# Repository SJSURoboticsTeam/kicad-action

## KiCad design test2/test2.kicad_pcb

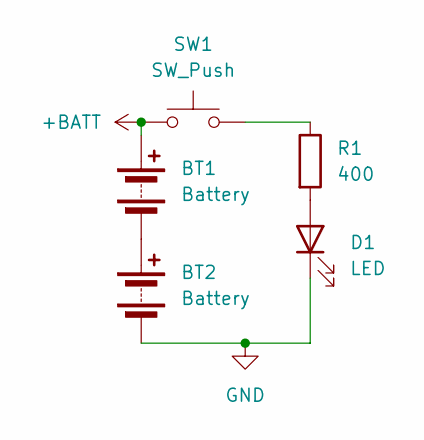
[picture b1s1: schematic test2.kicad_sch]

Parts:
BT1, BT2: Battery; BatteryHolder_Keystone_2466_1xAAA
D1: LED; LED_PLCC-2_3.4x3.0mm_KA
R1: 400; R_0603_1608Metric
SW1: SW_Push; SW_Push_1TS009xxxx-xxxx-xxxx_6x6x5mm

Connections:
+BATT: BT1.1 (+), SW1.1
GND: BT2.2 (-), D1.1 (K)
unnamed: BT1.2 (-), BT2.1 (+)
unnamed: D1.2 (A), R1.2
unnamed: R1.1, SW1.2

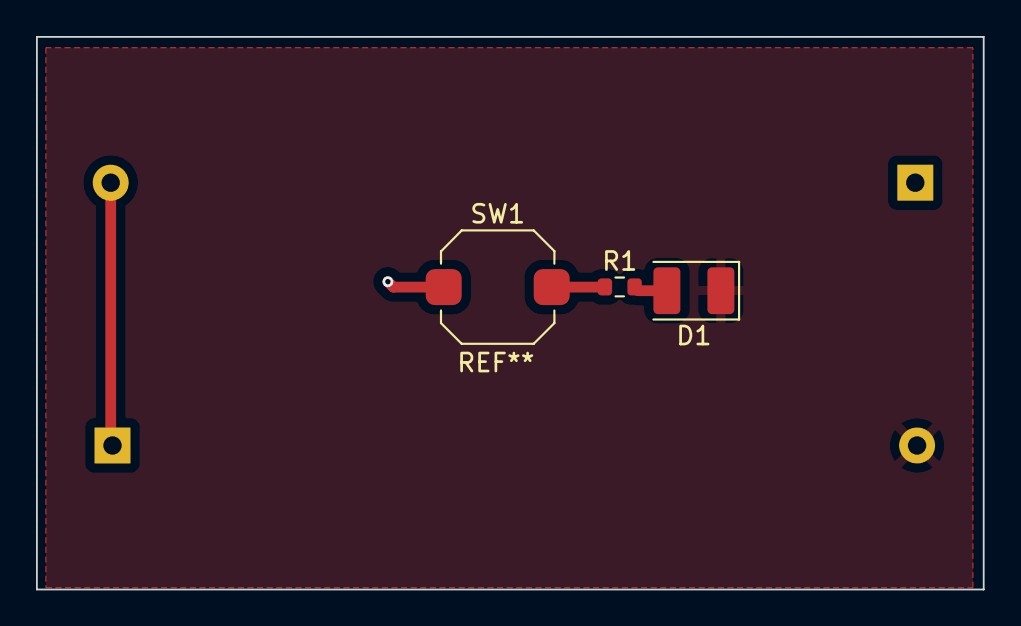
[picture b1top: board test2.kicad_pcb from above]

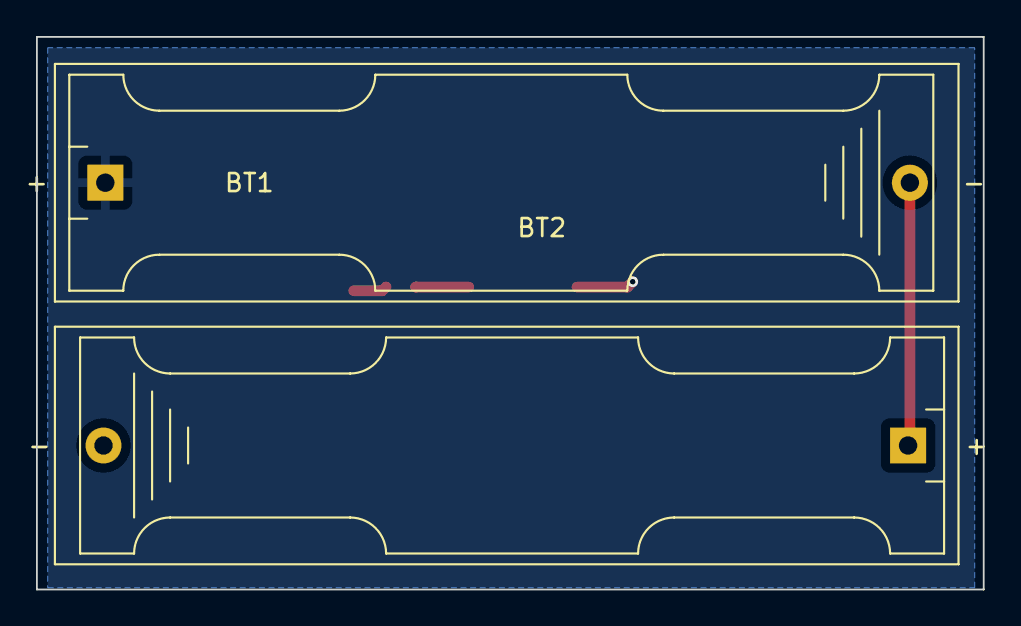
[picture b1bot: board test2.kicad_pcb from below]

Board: 2 copper layers, 52.6 x 30.7 mm, 5 parts (2 on the bottom side), 5 nets.

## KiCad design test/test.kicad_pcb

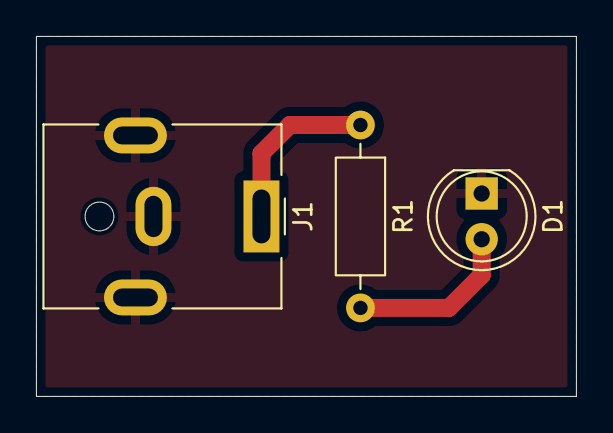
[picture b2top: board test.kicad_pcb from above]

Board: 2 copper layers, 30.0 x 20.0 mm, 3 parts (0 on the bottom side), 3 nets.

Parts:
D1: RED; LED_D5.0mm
J1: Barrel_Jack_MountingPin; BarrelJack_CUI_PJ-063AH_Horizontal
R1: 147Ω; R_Axial_DIN0207_L6.3mm_D2.5mm_P10.16mm_Horizontal

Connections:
+5V: J1.1, R1.1
GND: D1.1 (K), J1.2, J1.MP (MountPin)
unnamed: D1.2 (A), R1.2

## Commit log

2025-09-03 modify script to allow for multiple inputs, add test workflow for multiple inputs
2025-09-03 fix syntax errors
2025-09-03 debug errors
2025-09-03 fix filename error
2025-09-03 oops wrong dir
2025-09-03 update models so DRC does not fail
2025-09-03 fix preset bug by adding a preset
2025-09-03 fix preset type
2025-09-03 add format option, disable debugging
2025-10-25 add output directory
2025-10-25 update output directory
2025-10-25 try again
2025-10-26 test with multiline blocks
